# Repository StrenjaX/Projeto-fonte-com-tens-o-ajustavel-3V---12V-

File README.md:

# Projeto fonte com tensão ajustavel (3V-12V)
Trabalho 1 - Fonte

O objetivo deste projeto é fazer uma fonte com uma apartir de uma tensão alternada tendo que ser ajustavel entre 3 e 12 volts, com capacidade de 100mA.

Materia: Eletronica para computação.

Professor: Eduardo do Valle Simões.

Aluno: Osni Brito de Jesus 

NUSP: 11857330

| Componentes  |  Preço(R$)  |
| ------------------- | ------------------- |
|  [Diodo 1N5404 (até 3A)](https://www.baudaeletronica.com.br/diodo-1n5404.html) |  4 x 0,36 |
|  [Capacitor 470uf x 50V](https://www.eletrogate.com/capacitor-eletrolitico-470uf-x-50v?utm_source=Site&utm_medium=GoogleMerchant&utm_campaign=GoogleMerchant&gclid=EAIaIQobChMIwLCm0bbN6gIVjA6RCh1ObAOAEAkYASABEgJvCfD_BwE)  |  0,90 |
|  [Resistor 2,2k (1/4W)](https://www.baudaeletronica.com.br/resistor-2k2-5-1-4w.html) |  2 x 0,08 |
|  [Resistor 1,2k (1/4W)](https://www.baudaeletronica.com.br/resistor-1k2-5-1-4w.html) |  0,08 |
|  [Diodo Zener 1N4743 [13V / 1W]](https://www.baudaeletronica.com.br/diodo-zener-1n4743-13v-1w.html) |  0,20 |
|  [Potenciometro Linear 5K](https://www.americanas.com.br/produto/1486223377?sellerid=16569609000116&epar=%7Bifpla:%7B_epar%7D%7D%7Bifdyn:%7B_epar%7D%7D%7Bifdbm:ds_at_ov_db_acom$%7BCAMPAIGN_ID%7D%7D&opn=YSMESP&WT.srch=1) |  6,61 |
|  [Transformador 127v-220v](https://produto.mercadolivre.com.br/MLB-989883391-transformador-trafo-1212v-200ma-bivolt-eletronica-eletrica-_JM?quantity=1#position=1&type=item&tracking_id=9abf8c61-6492-4e02-bb1d-d1a22f9b055d) |  22,99 |
|   [Transistor NPN BC337 (de até 45v 500mAh)](https://www.baudaeletronica.com.br/transistor-npn-bc337.html)   |   0,17   |
| TOTAL |  R$ 32,55  |

## Projeto no Falstad
 
 [link do circuito FALSTAD](http://tinyurl.com/ya34tdqr)
 
## Projeto no EAGLE

## Projeto do EAGLE pronto para impressão na placa

 [Explicação no youtube aqui](https://www.youtube.com/watch?v=vDUC-hhlkVI&feature=youtu.be)

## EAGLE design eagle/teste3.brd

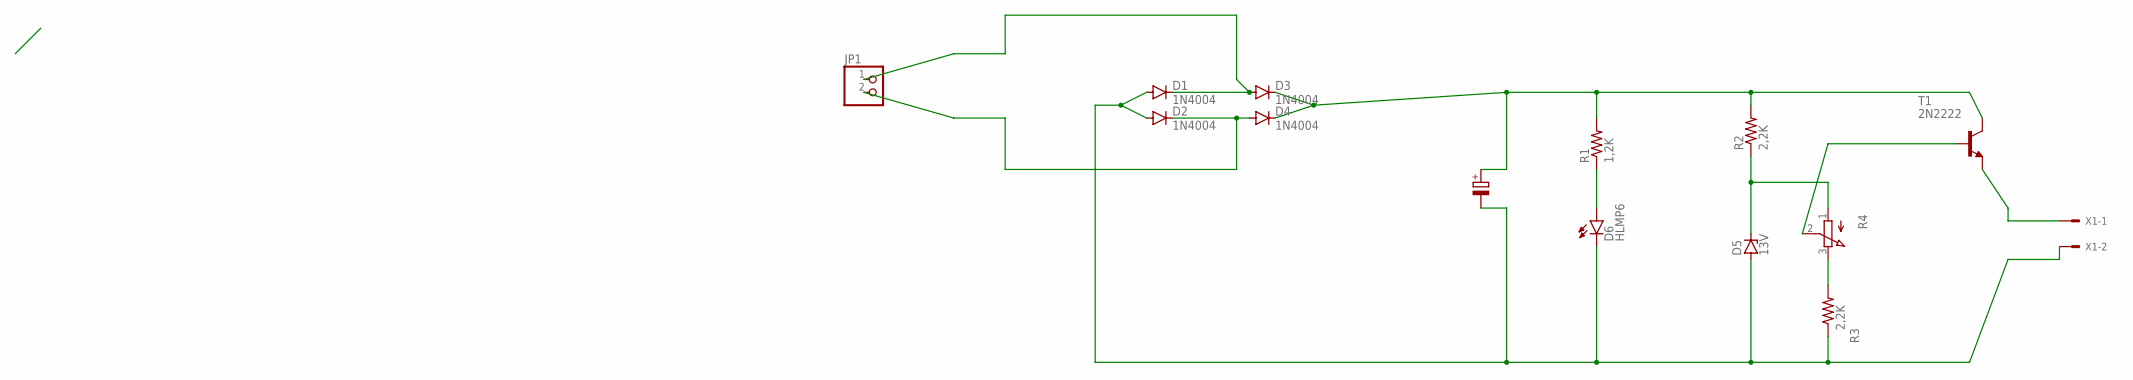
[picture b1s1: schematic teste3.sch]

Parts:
D1, D2, D3, D4: 1N4004; DO41-10
D5: 13V; SOD81
D6: HLMP6
JP1: PINHD-1X2; 1X02
R1: 1,2K; P0613/15
R2, R3: 2,2K; P0613/15
R4: 3RP/1610N
T1: 2N2222; TO18
X1: KK-156-2

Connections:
unnamed: D6.A, R1.1
unnamed: D1.A, D2.A, D5.A, D6.K, R3.1, X1.2
unnamed: D2.C, D4.A, JP1.2
unnamed: D3.C, D4.C, R1.2, R2.2, T1.3 (C)
unnamed: D5.C, R2.1, R4.1 (A)
unnamed: R3.2, R4.3 (E)
unnamed: R4.2 (S), T1.2 (B)
unnamed: T1.1 (E), X1.1
unnamed: D1.C, D3.A, JP1.1

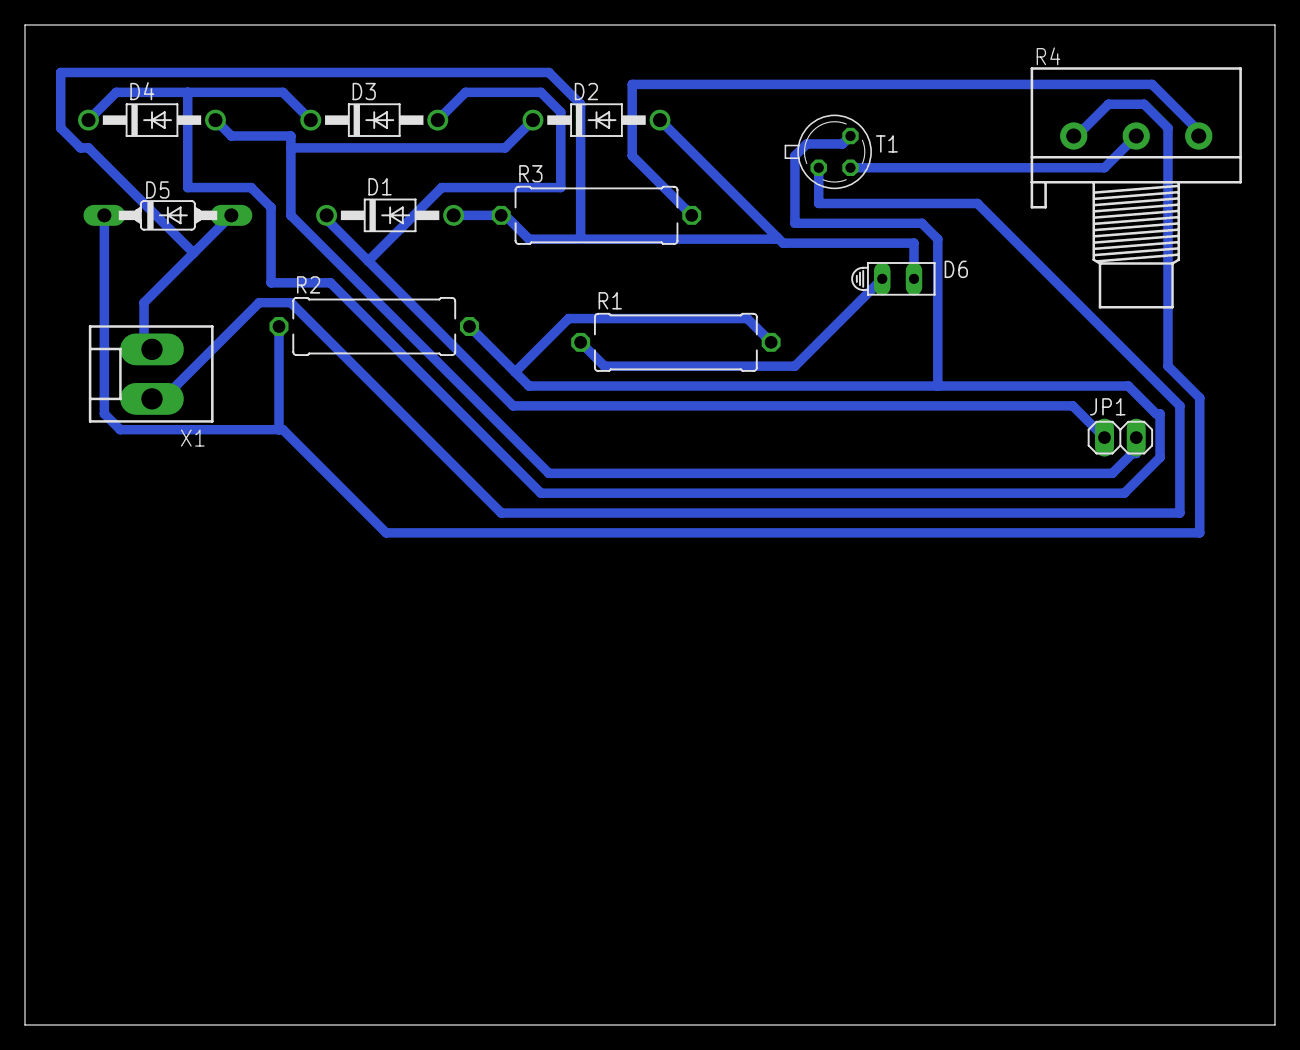
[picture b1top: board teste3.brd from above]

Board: 2 copper layers, 100.0 x 80.0 mm, 13 parts (0 on the bottom side), 9 nets.

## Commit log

2020-07-07 Create a
2020-07-07 Rename teste1.brd to eagle/teste1.brd
2020-07-07 Rename teste1.sch to eagle/teste1.sch
